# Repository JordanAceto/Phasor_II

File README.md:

# Phasor II Guitar Pedal

## 6-stage optical phase shifter pedal ala the Mu-tron II with extra features

- Fits in a Hammond BB style box
- Classic `RATE`, `DEPTH`, and `FEEDBACK` controls
- Powered by a standard guitar pedal style center-negative 9VDC power supply
- Expression pedal/CV input jack
    - Connect a Moog EP-3 or similar expression pedal with a TRS cable
    - Or inject a Control Voltage in the range [0v, +5v] with a TS cable
    - An internal jumper selects the destination for the modulation
        - `LFO DEPTH`
        - `LFO RATE`
        - `MANUAL SWEEP`

## [SCHEMATIC](https://github.com/JordanAceto/Phasor_II/blob/main/main_pcb/docs/phasor_II-schematic.pdf)

---

---

## Calibration
### There are three points of calibration via internal trimpots
- `EXP PEDAL TRIM`
    - Connect a Moog EP-3 or similar expression pedal to the `CV-PED` jack and power the pedal ON
    - Make sure that any built in attenuators on the expression pedal are turned all the way up
    - With a multimeter set to DC volts measure the TIP of the `CV-PED` jack relative to ground (there is a convenient place to clip the black lead of the multimeter on the pcb)
    - Sweep the expression pedal all the way forwards, and adjust the `EXP PEDAL TRIM` trimpot until you measure +5VDC
    - Sweep the expression pedal back and forth and observe that the tip of the `CV-PED` jack sweeps from 0v to +5v
    
- `DEPTH TRIM`
    - This sets the width of the phasor sweep
    - Adjust by ear so that the sweep width is pleasant

- `CENTER TRIM`
    - This sets the center of the phasor sweep
    - Adjust by ear so that the bottom "turn around" feels good

- The depth and center trims are somewhat interactive, and should be trimmed together iteratively. Try a variety of rate and depth settings while calibrating.

- Note that while there is a light shield covering the photocells, ambient light will slightly change the sweep when the back panel is off
    - Perform calibration in a dim room. It doesn't need to be pitch black, just avoid shining bright lights right onto the guts

### There are no wrong or harmful settings, adjust these to taste. If the expression pedal feels better to you with a different voltage across it, go nuts.

---

## Current consumed from the 9VDC power input
### 9VDC    :   200mA

---

## Status of the project:

Task | Status |
---------|--------------|
Schematic capture | &#9745;
PCB layout | &#9745;
Test build | &#9745;
Safe to order boards| &#9745;

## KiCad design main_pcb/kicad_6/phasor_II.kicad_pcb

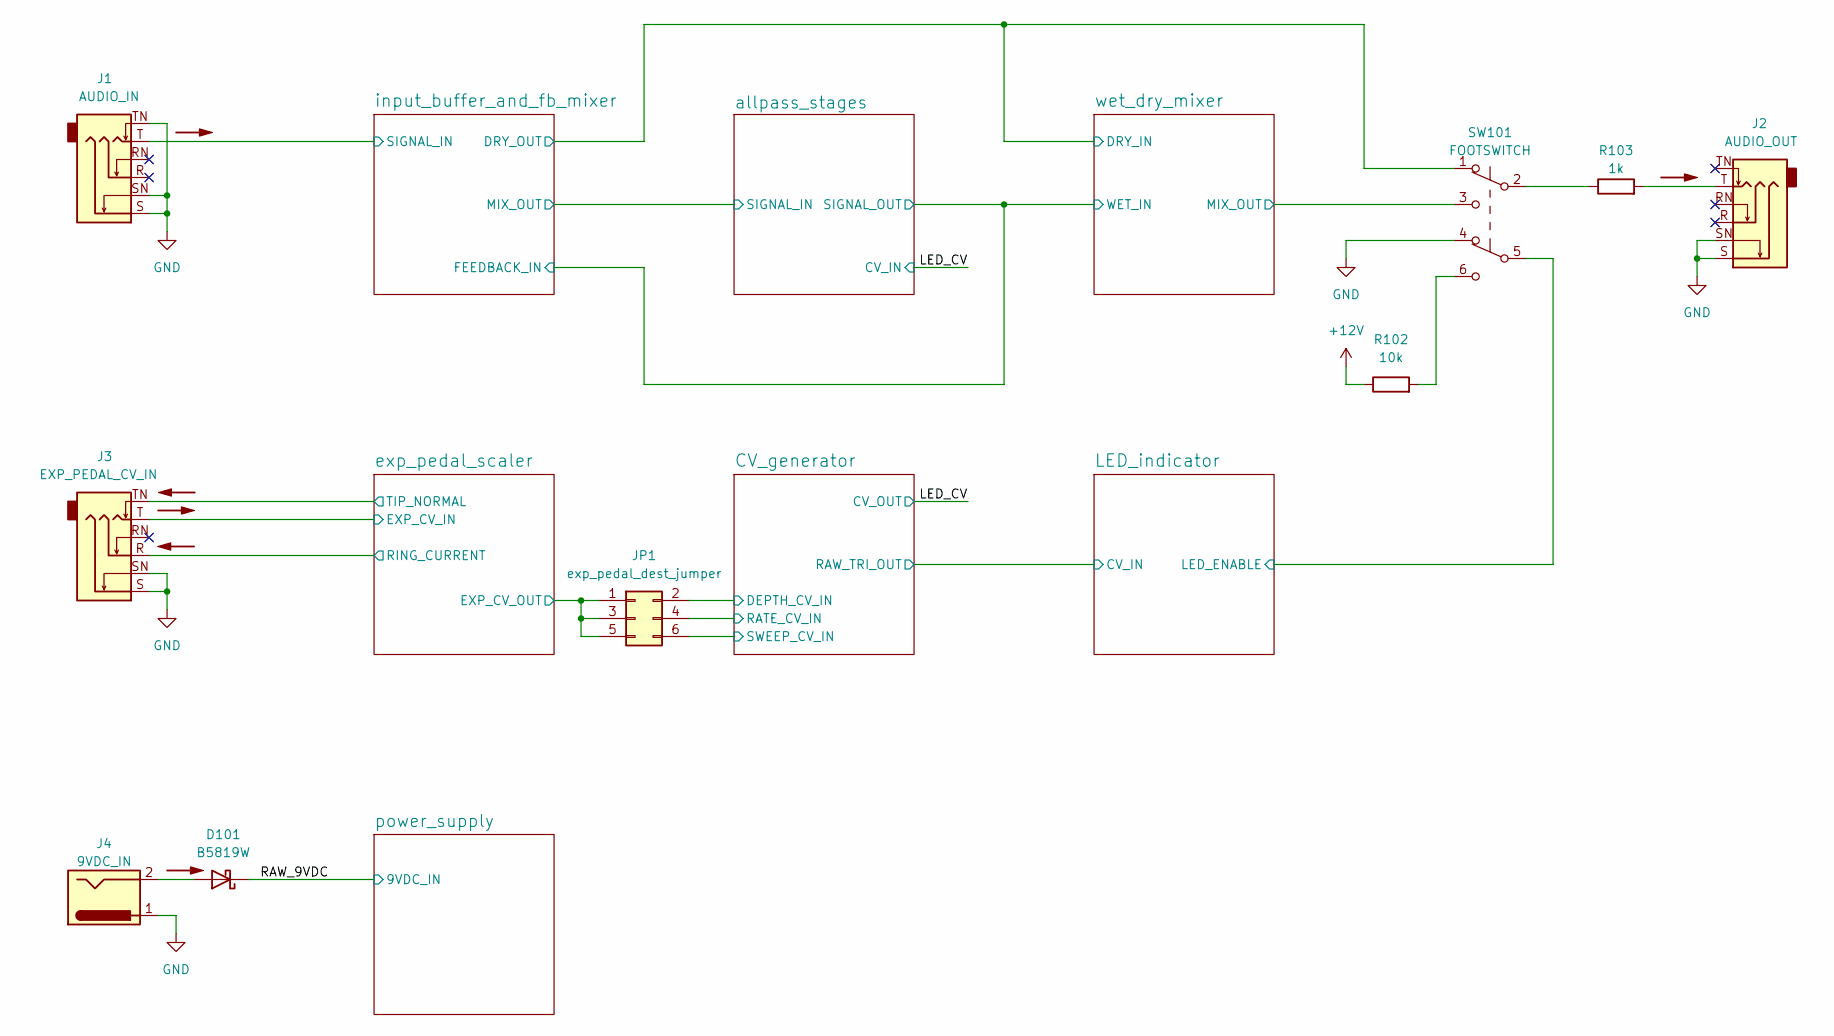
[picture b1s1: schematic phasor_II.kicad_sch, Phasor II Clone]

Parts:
D101: B5819W; D_SOD-123
J1: AUDIO_IN; Jack_6.35mm_Neutrik_NMJ6HCD2_Horizontal
J2: AUDIO_OUT; Jack_6.35mm_Neutrik_NMJ6HCD2_Horizontal
J3: EXP_PEDAL_CV_IN; Jack_6.35mm_Neutrik_NMJ6HCD2_Horizontal
J4: 9VDC_IN; BarrelJack_CUI_PJ-063AH_Horizontal
JP1: exp_pedal_dest_jumper; PinHeader_2x03_P2.54mm_Vertical
R102: 10k; R_0603_1608Metric
R103: 1k; R_0603_1608Metric
SW101: FOOTSWITCH; PinHeader_1x06_P2.54mm_Vertical

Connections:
+12V: R102.1; also elsewhere on the board
/CV_generator/DEPTH_CV_IN: JP1.2; also elsewhere on the board
/CV_generator/RATE_CV_IN: JP1.4; also elsewhere on the board
/CV_generator/SWEEP_CV_IN: JP1.6; also elsewhere on the board
/LED_indicator/LED_ENABLE: SW101.5 (B); also elsewhere on the board
/RAW_9VDC: D101.1 (K); also elsewhere on the board
/exp_pedal_scaler/EXP_CV_IN: J3.T; also elsewhere on the board
/exp_pedal_scaler/EXP_CV_OUT: JP1.1, JP1.3, JP1.5; also elsewhere on the board
/exp_pedal_scaler/RING_CURRENT: J3.R; also elsewhere on the board
/exp_pedal_scaler/TIP_NORMAL: J3.TN; also elsewhere on the board
/input_buffer_and_fb_mixer/DRY_OUT: SW101.1 (A); also elsewhere on the board
/input_buffer_and_fb_mixer/SIGNAL_IN: J1.T; also elsewhere on the board
/wet_dry_mixer/MIX_OUT: SW101.3 (C); also elsewhere on the board
GND: J1.S, J1.SN, J1.TN, J2.S, J2.SN, J3.S, J3.SN, J4.1, SW101.4 (A); also elsewhere on the board
unnamed: D101.2 (A), J4.2
unnamed: J2.T, R103.2
unnamed: R102.2, SW101.6 (C)
unnamed: R103.1, SW101.2 (B)

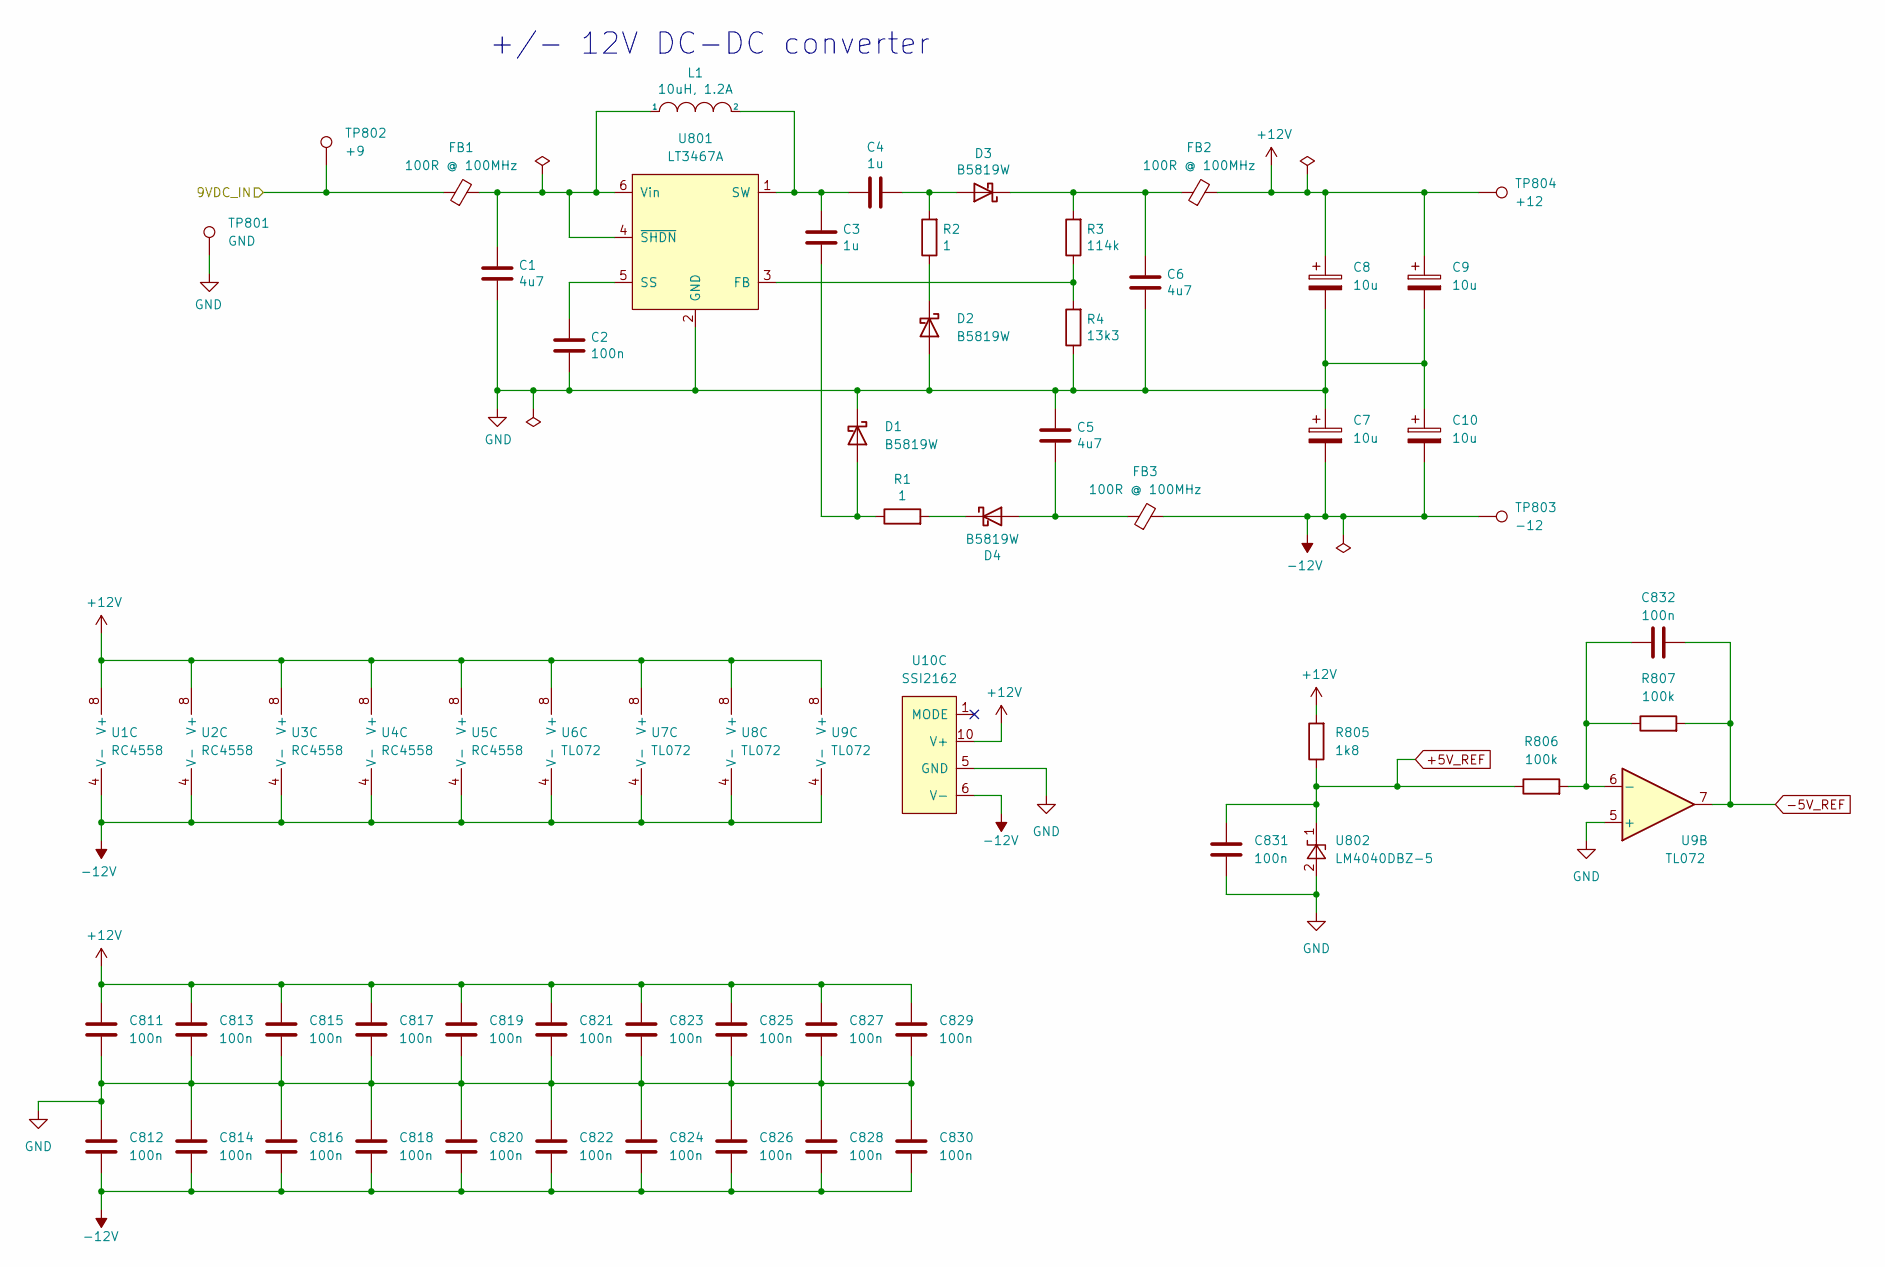
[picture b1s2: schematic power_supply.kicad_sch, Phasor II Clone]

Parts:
C1, C5, C6: 4u7; C_0805_2012Metric
C2, C811, C812, C813, C814, C815, C816, C817, C818, C819, C820, C821, C822, C823, C824, C825, C826, C827, C828, C829, C830, C831, C832: 100n; C_0603_1608Metric
C3, C4: 1u; C_0805_2012Metric
C7, C8, C9, C10: 10u; CP_Radial_D6.3mm_P2.50mm
D1, D2, D3, D4: B5819W; D_SOD-123
FB1, FB2, FB3: 100R @ 100MHz; L_0805_2012Metric
L1: 10uH, 1.2A; L_Taiyo-Yuden_NR-50xx
R1, R2: 1; R_0603_1608Metric
R3: 114k; R_0603_1608Metric
R4: 13k3; R_0603_1608Metric
R805: 1k8; R_0603_1608Metric
R806, R807: 100k; R_0603_1608Metric
TP801: GND; TestPoint_Bridge_Pitch7.62mm_Drill1.3mm
TP802: +9; TestPoint_Keystone_5000-5004_Miniature
TP803: -12; TestPoint_Keystone_5000-5004_Miniature
TP804: +12; TestPoint_Keystone_5000-5004_Miniature
U1, U2, U3, U4, U5: RC4558; SOIC-8_3.9x4.9mm_P1.27mm
U6, U7, U8, U9: TL072; SOIC-8_3.9x4.9mm_P1.27mm
U10: SSI2162; SSOP-10_3.9x4.9mm_P1.00mm
U801: LT3467A; TSOT-23-6
U802: LM4040DBZ-5; SOT-23

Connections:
+5V_REF: C831.1, R805.1, R806.1, U802.1 (K); also elsewhere on the board
+12V: C8.1, C9.1, C811.1, C813.1, C815.1, C817.1, C819.1, C821.1, C823.1, C825.1, C827.1, C829.1, FB2.2, R805.2, TP804.1, U1.8 (V+), U2.8 (V+), U3.8 (V+), U4.8 (V+), U5.8 (V+), U6.8 (V+), U7.8 (V+), U8.8 (V+), U9.8 (V+), U10.10 (V+); also elsewhere on the board
-5V_REF: C832.1, R807.2, U9.7; also elsewhere on the board
-12V: C7.2, C10.2, C812.2, C814.2, C816.2, C818.2, C820.2, C822.2, C824.2, C826.2, C828.2, C830.2, FB3.2, TP803.1, U1.4 (V-), U2.4 (V-), U3.4 (V-), U4.4 (V-), U5.4 (V-), U6.4 (V-), U7.4 (V-), U8.4 (V-), U9.4 (V-), U10.6 (V-)
/RAW_9VDC: FB1.1, TP802.1; also elsewhere on the board
GND: C1.2, C2.2, C5.1, C6.2, C7.1, C8.2, C9.2, C10.1, C811.2, C812.1, C813.2, C814.1, C815.2, C816.1, C817.2, C818.1, C819.2, C820.1, C821.2, C822.1, C823.2, C824.1, C825.2, C826.1, C827.2, C828.1, C829.2, C830.1, C831.2, D1.1 (K), D2.2 (A), R4.1, TP801.1, U9.5 (+), U10.5 (GND), U801.2 (GND), U802.2 (A); also elsewhere on the board
unnamed: C1.1, FB1.2, L1.1, U801.4 (~SHDN), U801.6 (Vin)
unnamed: C2.1, U801.5 (SS)
unnamed: C3.1, C4.2, L1.2, U801.1 (SW)
unnamed: C3.2, D1.2 (A), R1.1
unnamed: C4.1, D3.2 (A), R2.2
unnamed: C5.2, D4.2 (A), FB3.1
unnamed: C6.1, D3.1 (K), FB2.1, R3.2
unnamed: C832.2, R806.2, R807.1, U9.6 (-)
unnamed: D2.1 (K), R2.1
unnamed: D4.1 (K), R1.2
unnamed: R3.1, R4.2, U801.3 (FB)

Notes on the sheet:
+/- 12V DC-DC converter

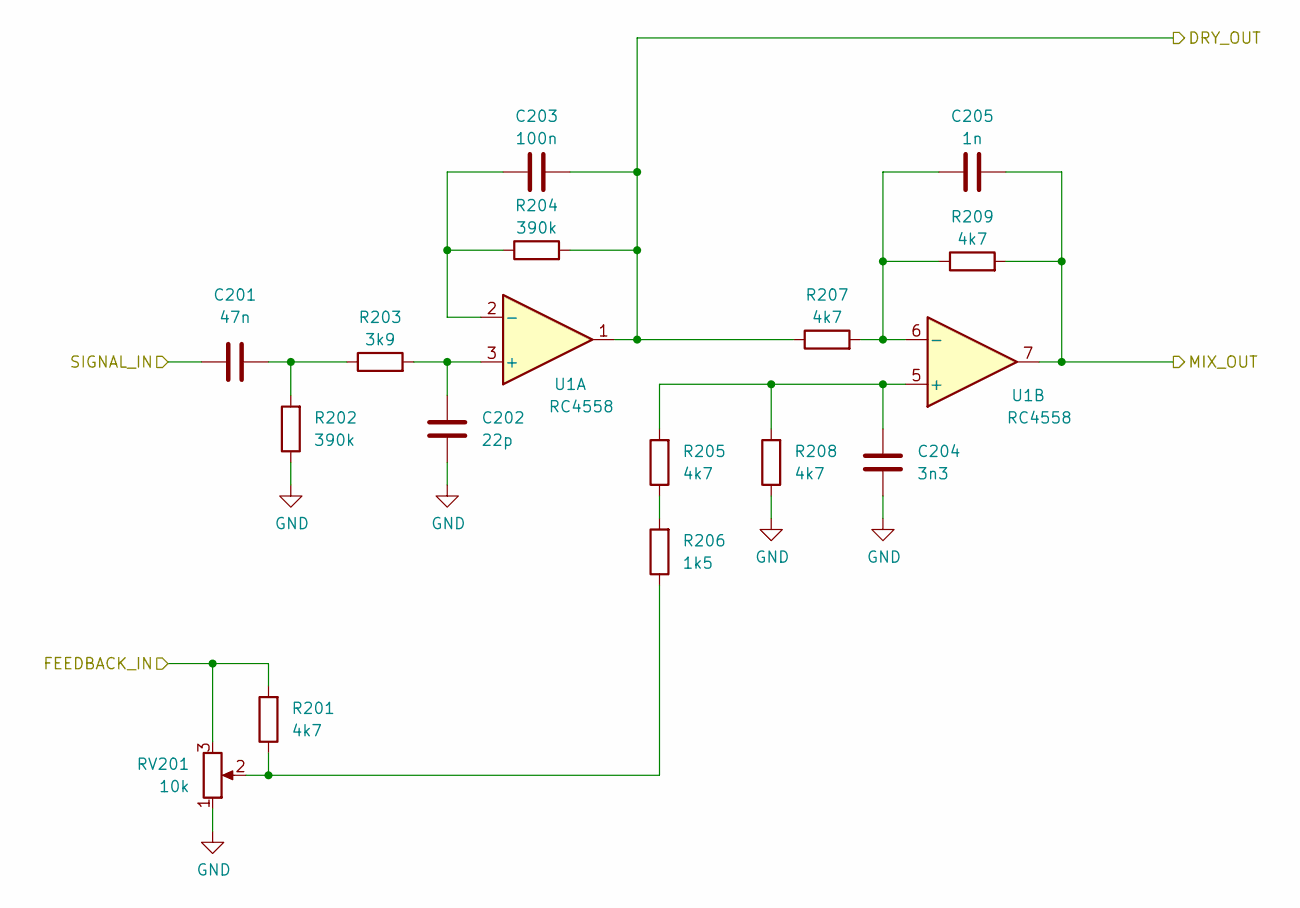
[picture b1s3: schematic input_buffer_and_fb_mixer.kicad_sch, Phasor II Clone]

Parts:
C201: 47n; C_Rect_L7.0mm_W2.5mm_P5.00mm
C202: 22p; C_0603_1608Metric
C203: 100n; C_0603_1608Metric
C204: 3n3; C_0603_1608Metric
C205: 1n; C_0603_1608Metric
R201, R205, R207, R208, R209: 4k7; R_0603_1608Metric
R202, R204: 390k; R_0603_1608Metric
R203: 3k9; R_0603_1608Metric
R206: 1k5; R_0603_1608Metric
RV201: 10k; Potentiometer_Alpha_RD901F-40-00D_Single_Vertical
U1: RC4558; SOIC-8_3.9x4.9mm_P1.27mm

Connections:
/allpass_stages/SIGNAL_IN: C205.2, R209.2, U1.7; also elsewhere on the board
/allpass_stages/SIGNAL_OUT: R201.2, RV201.3; also elsewhere on the board
/input_buffer_and_fb_mixer/DRY_OUT: C203.2, R204.2, R207.1, U1.1; also elsewhere on the board
/input_buffer_and_fb_mixer/SIGNAL_IN: C201.1; also elsewhere on the board
GND: C202.2, C204.2, R202.1, R208.1, RV201.1; also elsewhere on the board
unnamed: C201.2, R202.2, R203.1
unnamed: C202.1, R203.2, U1.3 (+)
unnamed: C203.1, R204.1, U1.2 (-)
unnamed: C204.1, R205.2, R208.2, U1.5 (+)
unnamed: C205.1, R207.2, R209.1, U1.6 (-)
unnamed: R201.1, R206.1, RV201.2
unnamed: R205.1, R206.2

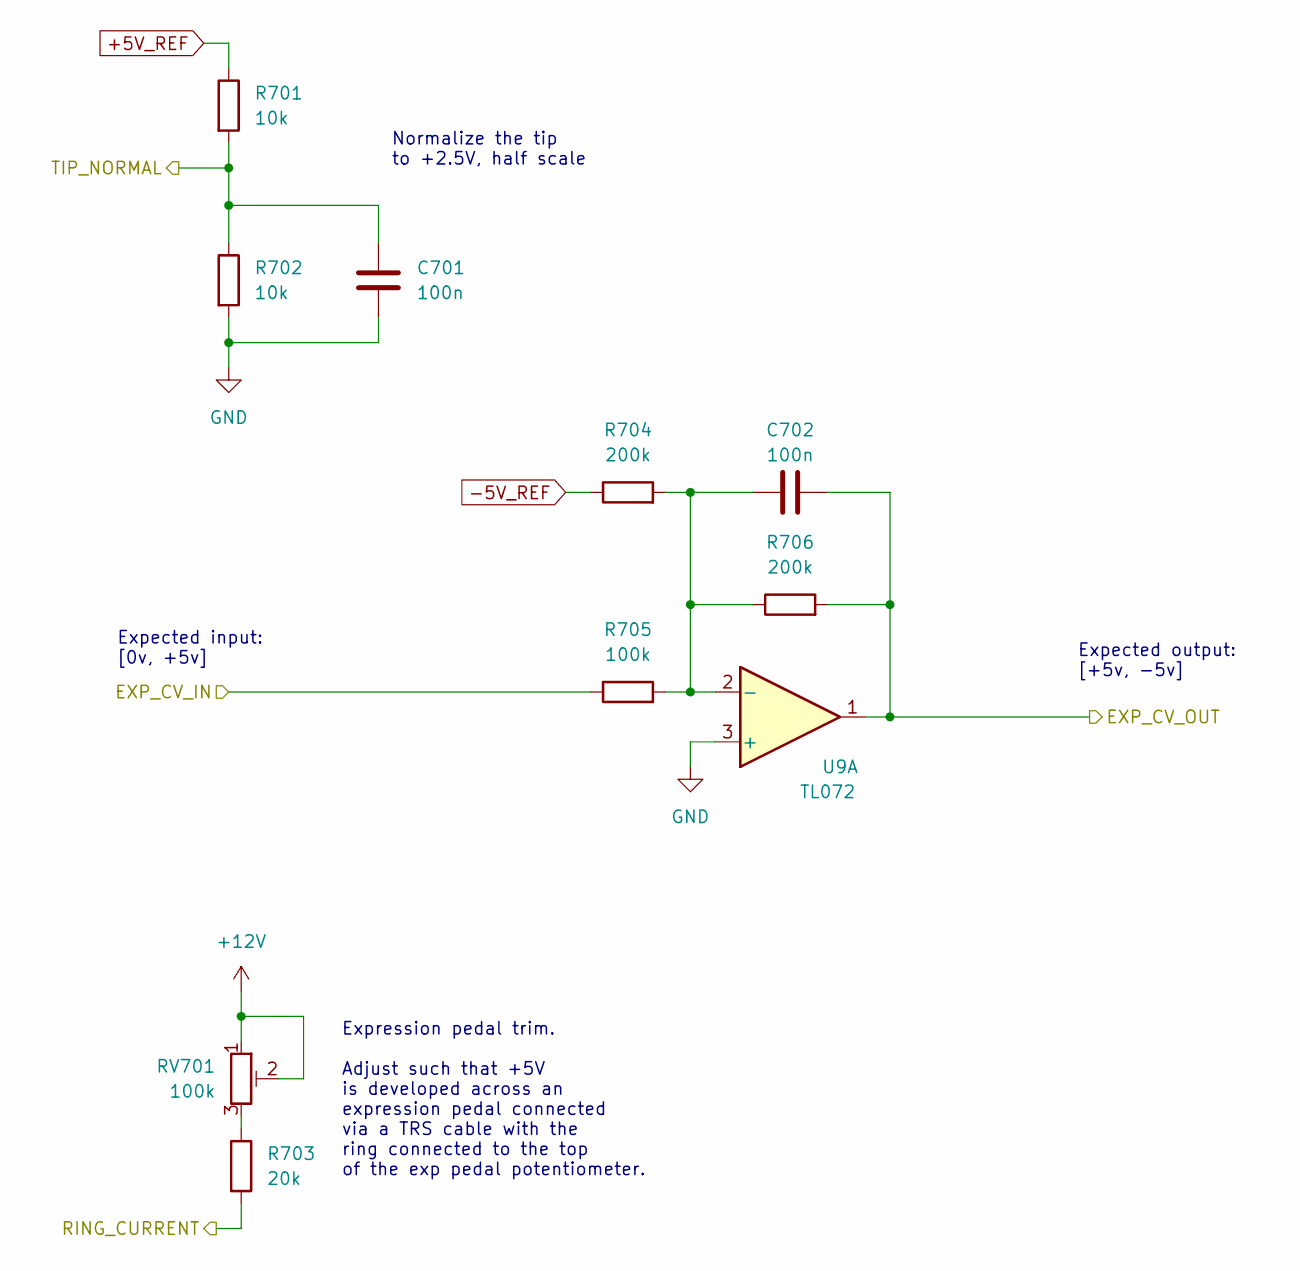
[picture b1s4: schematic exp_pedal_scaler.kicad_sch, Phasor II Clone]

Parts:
C701, C702: 100n; C_0603_1608Metric
R701, R702: 10k; R_0603_1608Metric
R703: 20k; R_0603_1608Metric
R704, R706: 200k; R_0603_1608Metric
R705: 100k; R_0603_1608Metric
RV701: 100k; Potentiometer_Bourns_3296W_Vertical
U9: TL072; SOIC-8_3.9x4.9mm_P1.27mm

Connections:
+5V_REF: R701.1; also elsewhere on the board
+12V: RV701.1, RV701.2; also elsewhere on the board
-5V_REF: R704.1; also elsewhere on the board
/exp_pedal_scaler/EXP_CV_IN: R705.1; also elsewhere on the board
/exp_pedal_scaler/EXP_CV_OUT: C702.1, R706.2, U9.1; also elsewhere on the board
/exp_pedal_scaler/RING_CURRENT: R703.2; also elsewhere on the board
/exp_pedal_scaler/TIP_NORMAL: C701.1, R701.2, R702.1; also elsewhere on the board
GND: C701.2, R702.2, U9.3 (+); also elsewhere on the board
unnamed: C702.2, R704.2, R705.2, R706.1, U9.2 (-)
unnamed: R703.1, RV701.3

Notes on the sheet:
Expected input: [0v, +5v]
Normalize the tip to +2.5V, half scale
Expected output: [+5v, -5v]
Expression pedal trim. Adjust such that +5V is developed across an expression pedal connected via a TRS cable with the ring connected to the top of the exp pedal potentiometer.

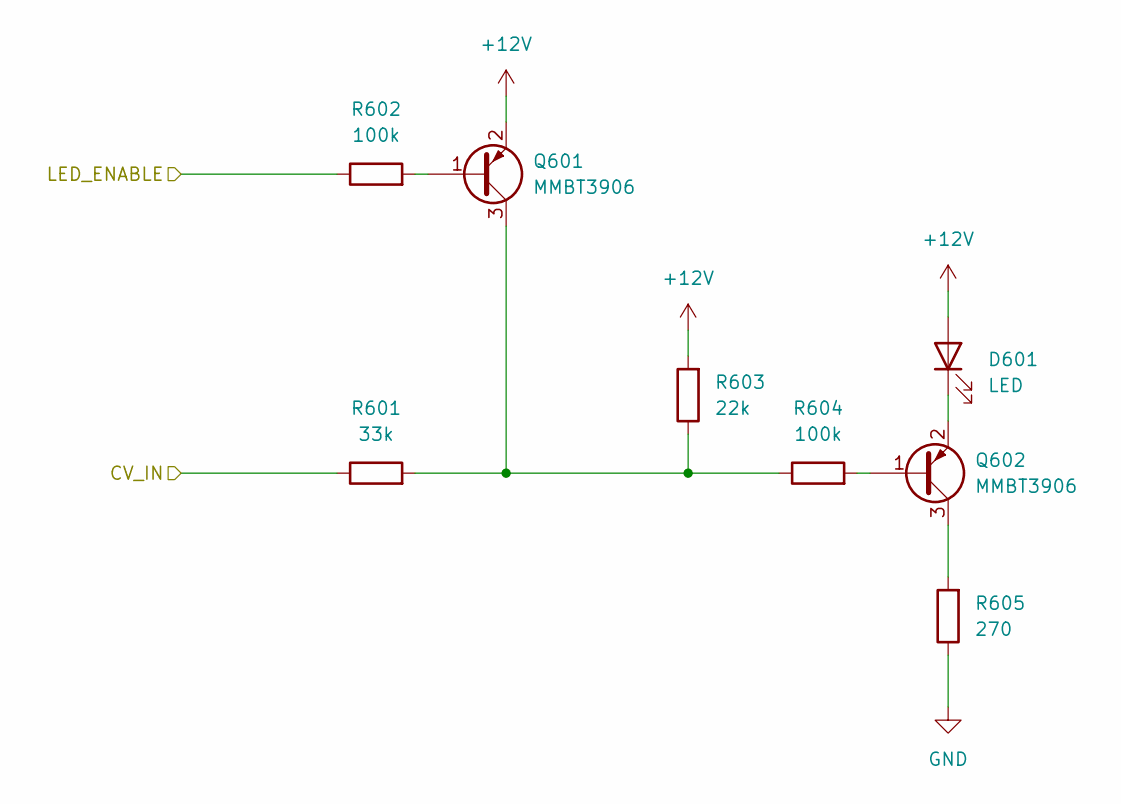
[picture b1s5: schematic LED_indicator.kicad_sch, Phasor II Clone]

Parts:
D601: LED; LED_D5.0mm
Q601, Q602: MMBT3906; SOT-23
R601: 33k; R_0603_1608Metric
R602, R604: 100k; R_0603_1608Metric
R603: 22k; R_0603_1608Metric
R605: 270; R_0603_1608Metric

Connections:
+12V: D601.2 (A), Q601.2 (E), R603.2; also elsewhere on the board
/CV_generator/RAW_TRI_OUT: R601.1; also elsewhere on the board
/LED_indicator/LED_ENABLE: R602.1; also elsewhere on the board
GND: R605.1; also elsewhere on the board
unnamed: D601.1 (K), Q602.2 (E)
unnamed: Q601.1 (B), R602.2
unnamed: Q601.3 (C), R601.2, R603.1, R604.1
unnamed: Q602.1 (B), R604.2
unnamed: Q602.3 (C), R605.2

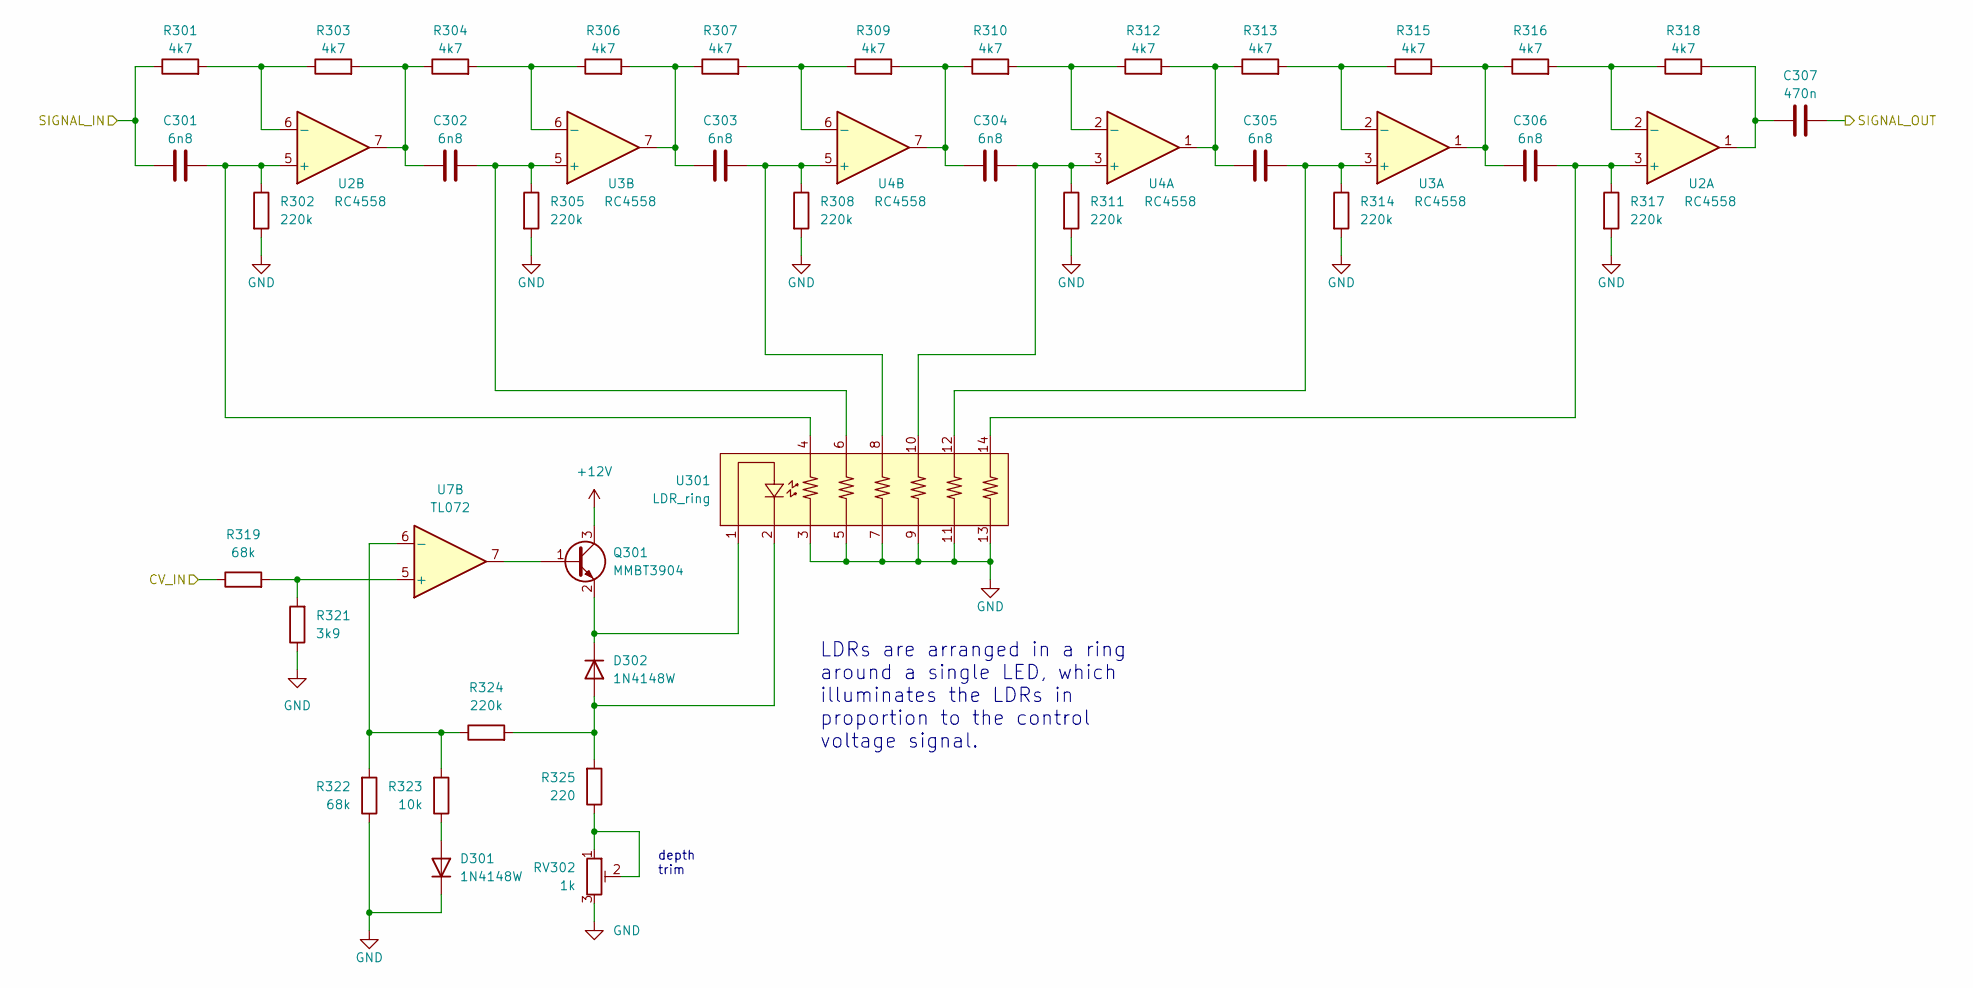
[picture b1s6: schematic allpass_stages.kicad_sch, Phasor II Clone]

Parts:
C301, C302, C303, C304, C305, C306: 6n8; C_0805_2012Metric
C307: 470n; C_Rect_L7.0mm_W3.5mm_P5.00mm
D301, D302: 1N4148W; D_SOD-123
Q301: MMBT3904; SOT-23
R301, R303, R304, R306, R307, R309, R310, R312, R313, R315, R316, R318: 4k7; R_0603_1608Metric
R302, R305, R308, R311, R314, R317, R324: 220k; R_0603_1608Metric
R319, R322: 68k; R_0603_1608Metric
R321: 3k9; R_0603_1608Metric
R323: 10k; R_0603_1608Metric
R325: 220; R_0603_1608Metric
RV302: 1k; Potentiometer_Bourns_3296W_Vertical
U2, U3, U4: RC4558; SOIC-8_3.9x4.9mm_P1.27mm
U7: TL072; SOIC-8_3.9x4.9mm_P1.27mm
U301: LDR_ring

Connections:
+12V: Q301.3 (C); also elsewhere on the board
/LED_CV: R319.1; also elsewhere on the board
/allpass_stages/SIGNAL_IN: C301.1, R301.1; also elsewhere on the board
/allpass_stages/SIGNAL_OUT: C307.2; also elsewhere on the board
GND: D301.1 (K), R302.2, R305.2, R308.2, R311.2, R314.2, R317.2, R321.1, R322.1, RV302.3, U301.3, U301.5, U301.7, U301.9, U301.11, U301.13; also elsewhere on the board
unnamed: C301.2, R302.1, U2.5 (+), U301.4
unnamed: C302.1, R303.2, R304.1, U2.7
unnamed: C302.2, R305.1, U3.5 (+), U301.6
unnamed: C303.1, R306.2, R307.1, U3.7
unnamed: C303.2, R308.1, U4.5 (+), U301.8
unnamed: C304.1, R309.2, R310.1, U4.7
unnamed: C304.2, R311.1, U4.3 (+), U301.10
unnamed: C305.1, R312.2, R313.1, U4.1
unnamed: C305.2, R314.1, U3.3 (+), U301.12
unnamed: C306.1, R315.2, R316.1, U3.1
unnamed: C306.2, R317.1, U2.3 (+), U301.14
unnamed: C307.1, R318.2, U2.1
unnamed: D301.2 (A), R323.1
unnamed: D302.1 (K), Q301.2 (E), U301.1
unnamed: D302.2 (A), R324.2, R325.2, U301.2
unnamed: Q301.1 (B), U7.7
unnamed: R301.2, R303.1, U2.6 (-)
unnamed: R304.2, R306.1, U3.6 (-)
unnamed: R307.2, R309.1, U4.6 (-)
unnamed: R310.2, R312.1, U4.2 (-)
unnamed: R313.2, R315.1, U3.2 (-)
unnamed: R316.2, R318.1, U2.2 (-)
unnamed: R319.2, R321.2, U7.5 (+)
unnamed: R322.2, R323.2, R324.1, U7.6 (-)
unnamed: R325.1, RV302.1, RV302.2

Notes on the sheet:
LDRs are arranged in a ring around a single LED, which illuminates the LDRs in proportion to the control voltage signal.
depth trim

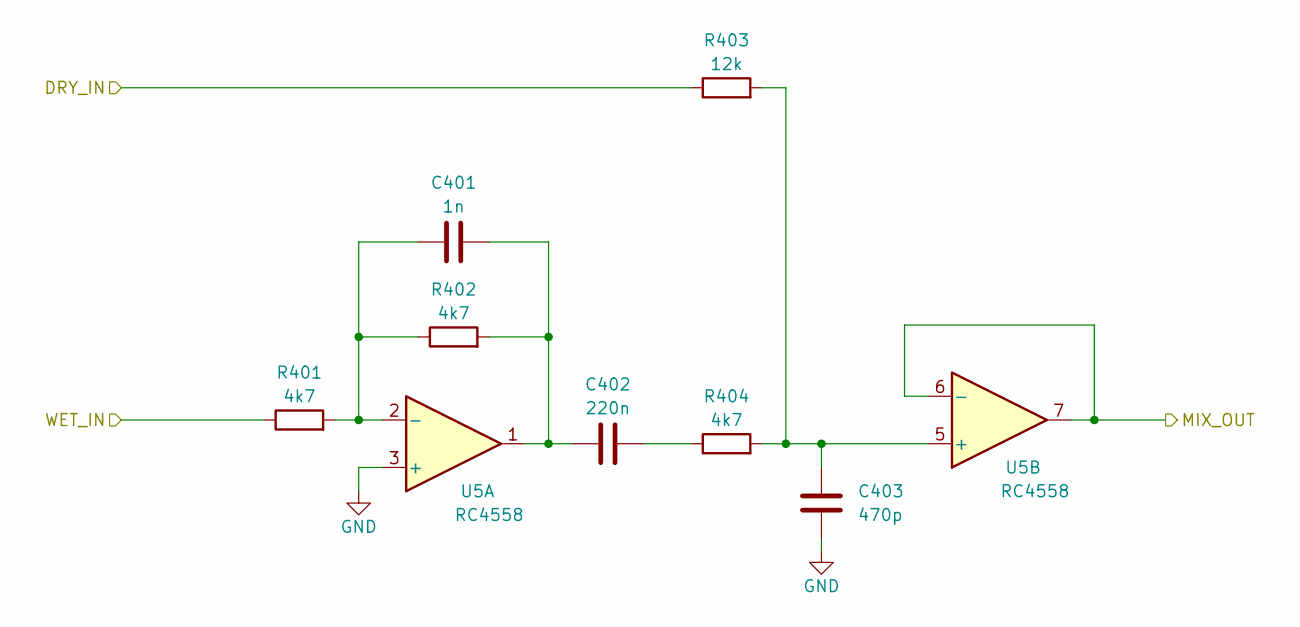
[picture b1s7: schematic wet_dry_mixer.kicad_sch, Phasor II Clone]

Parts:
C401: 1n; C_0603_1608Metric
C402: 220n; C_Rect_L7.0mm_W2.5mm_P5.00mm
C403: 470p; C_0603_1608Metric
R401, R402, R404: 4k7; R_0603_1608Metric
R403: 12k; R_0603_1608Metric
U5: RC4558; SOIC-8_3.9x4.9mm_P1.27mm

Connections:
/allpass_stages/SIGNAL_OUT: R401.1; also elsewhere on the board
/input_buffer_and_fb_mixer/DRY_OUT: R403.1; also elsewhere on the board
/wet_dry_mixer/MIX_OUT: U5.6 (-), U5.7; also elsewhere on the board
GND: C403.2, U5.3 (+); also elsewhere on the board
unnamed: C401.1, R401.2, R402.1, U5.2 (-)
unnamed: C401.2, C402.1, R402.2, U5.1
unnamed: C402.2, R404.1
unnamed: C403.1, R403.2, R404.2, U5.5 (+)

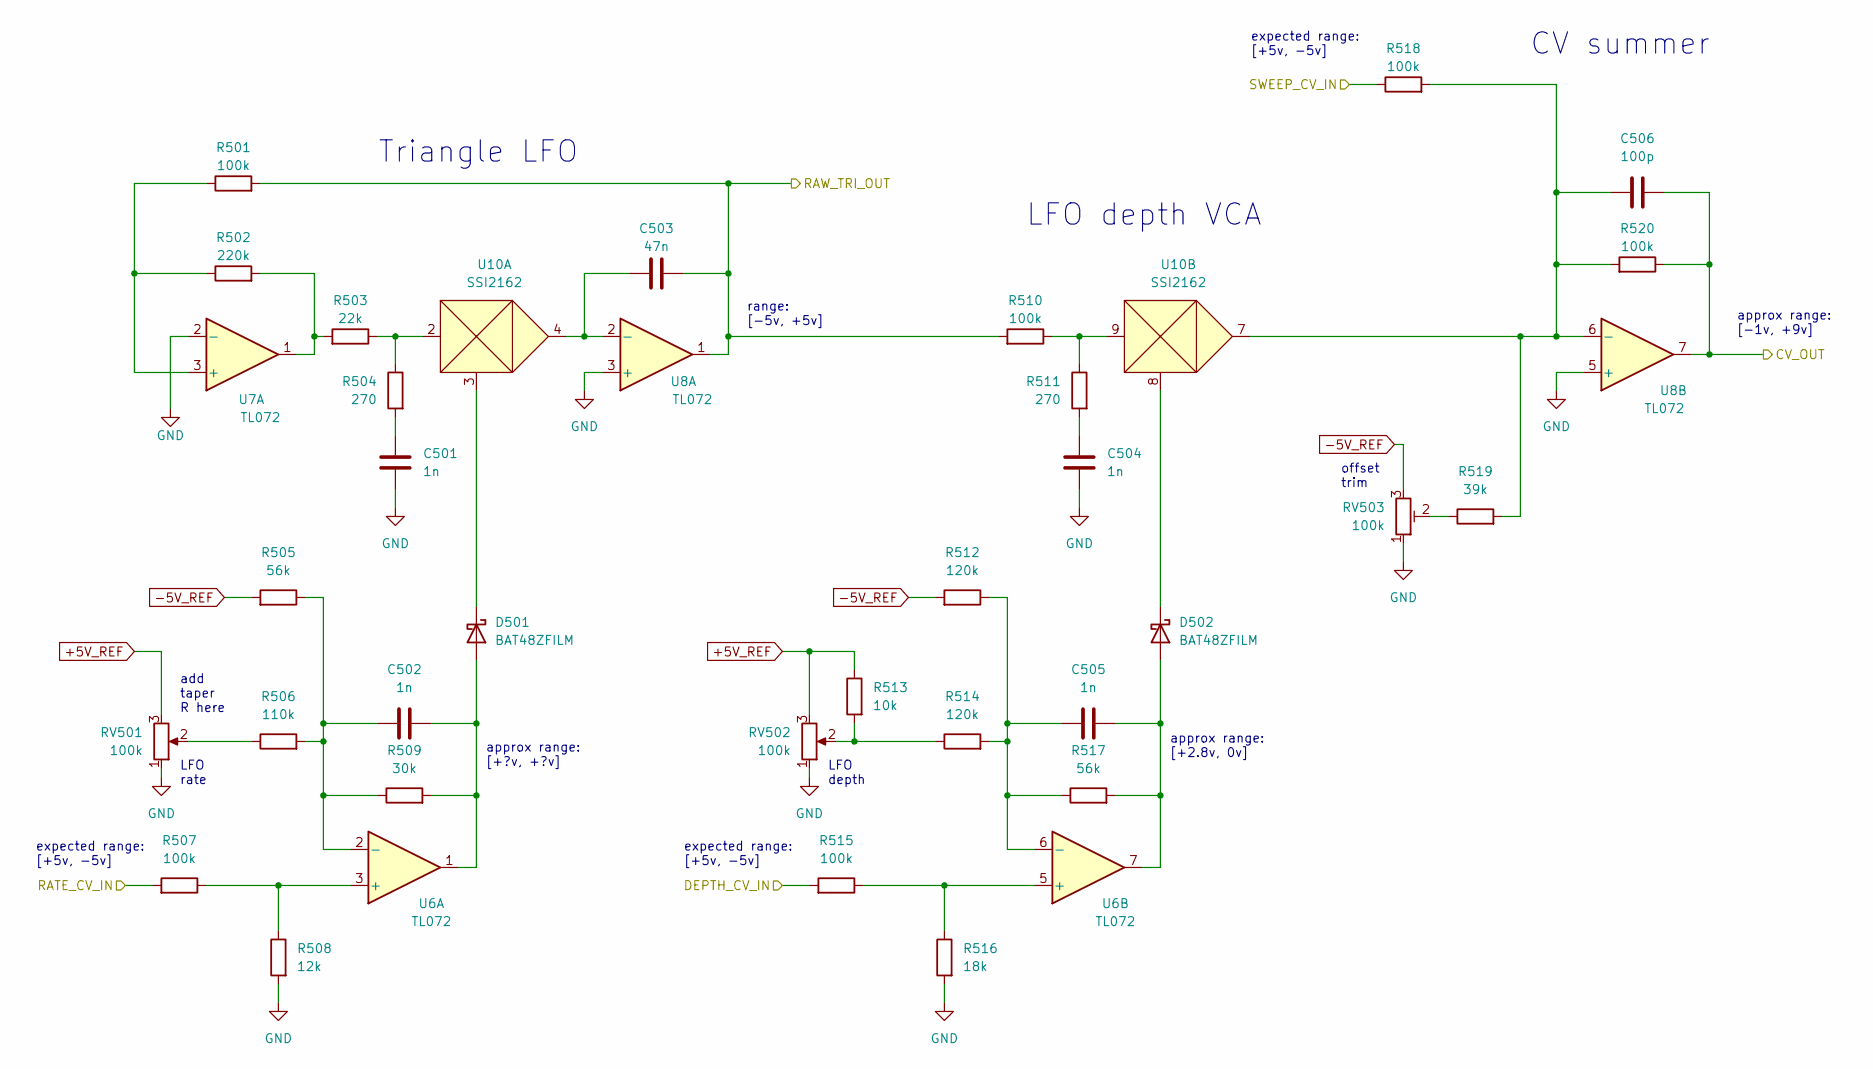
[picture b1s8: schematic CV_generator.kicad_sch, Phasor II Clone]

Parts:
C501, C502, C504, C505: 1n; C_0603_1608Metric
C503: 47n; C_0805_2012Metric
C506: 100p; C_0603_1608Metric
D501, D502: BAT48ZFILM; D_SOD-123
R501, R507, R510, R515, R518, R520: 100k; R_0603_1608Metric
R502: 220k; R_0603_1608Metric
R503: 22k; R_0603_1608Metric
R504, R511: 270; R_0603_1608Metric
R505, R517: 56k; R_0603_1608Metric
R506: 110k; R_0603_1608Metric
R508: 12k; R_0603_1608Metric
R509: 30k; R_0603_1608Metric
R512, R514: 120k; R_0603_1608Metric
R513: 10k; R_0603_1608Metric
R516: 18k; R_0603_1608Metric
R519: 39k; R_0603_1608Metric
RV501, RV502: 100k; Potentiometer_Alpha_RD901F-40-00D_Single_Vertical
RV503: 100k; Potentiometer_Bourns_3296W_Vertical
U6, U7, U8: TL072; SOIC-8_3.9x4.9mm_P1.27mm
U10: SSI2162; SSOP-10_3.9x4.9mm_P1.00mm

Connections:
+5V_REF: R513.1, RV501.3, RV502.3; also elsewhere on the board
-5V_REF: R505.2, R512.2, RV503.3; also elsewhere on the board
/CV_generator/DEPTH_CV_IN: R515.2; also elsewhere on the board
/CV_generator/RATE_CV_IN: R507.2; also elsewhere on the board
/CV_generator/RAW_TRI_OUT: C503.2, R501.2, R510.2, U8.1; also elsewhere on the board
/CV_generator/SWEEP_CV_IN: R518.1; also elsewhere on the board
/LED_CV: C506.1, R520.1, U8.7; also elsewhere on the board
GND: C501.2, C504.2, R508.2, R516.2, RV501.1, RV502.1, RV503.1, U7.2 (-), U8.3 (+), U8.5 (+); also elsewhere on the board
unnamed: C501.1, R504.2
unnamed: C502.1, D501.2 (A), R509.2, U6.1
unnamed: C502.2, R505.1, R506.2, R509.1, U6.2 (-)
unnamed: C503.1, U8.2 (-), U10.4
unnamed: C504.1, R511.2
unnamed: C505.1, D502.2 (A), R517.2, U6.7
unnamed: C505.2, R512.1, R514.2, R517.1, U6.6 (-)
unnamed: C506.2, R518.2, R519.2, R520.2, U8.6 (-), U10.7
unnamed: D501.1 (K), U10.3
unnamed: D502.1 (K), U10.8
unnamed: R501.1, R502.1, U7.3 (+)
unnamed: R502.2, R503.2, U7.1
unnamed: R503.1, R504.1, U10.2
unnamed: R506.1, RV501.2
unnamed: R507.1, R508.1, U6.3 (+)
unnamed: R510.1, R511.1, U10.9
unnamed: R513.2, R514.1, RV502.2
unnamed: R515.1, R516.1, U6.5 (+)
unnamed: R519.1, RV503.2

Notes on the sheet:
approx range: [+?v, +?v]
LFO depth
CV summer
approx range: [+2.8v, 0v]
LFO rate
expected range: [+5v, -5v]
add taper R here
range: [-5v, +5v]
LFO depth VCA
offset trim
approx range: [-1v, +9v]
Triangle LFO

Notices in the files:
main_pcb/kicad_6/CV_generator.kicad_sch:
creativecommons.org/licenses/by/4.0
License: CC by 4.0:
main_pcb/kicad_6/phasor_II.kicad_pcb:
Licinse: CC by 4.0
